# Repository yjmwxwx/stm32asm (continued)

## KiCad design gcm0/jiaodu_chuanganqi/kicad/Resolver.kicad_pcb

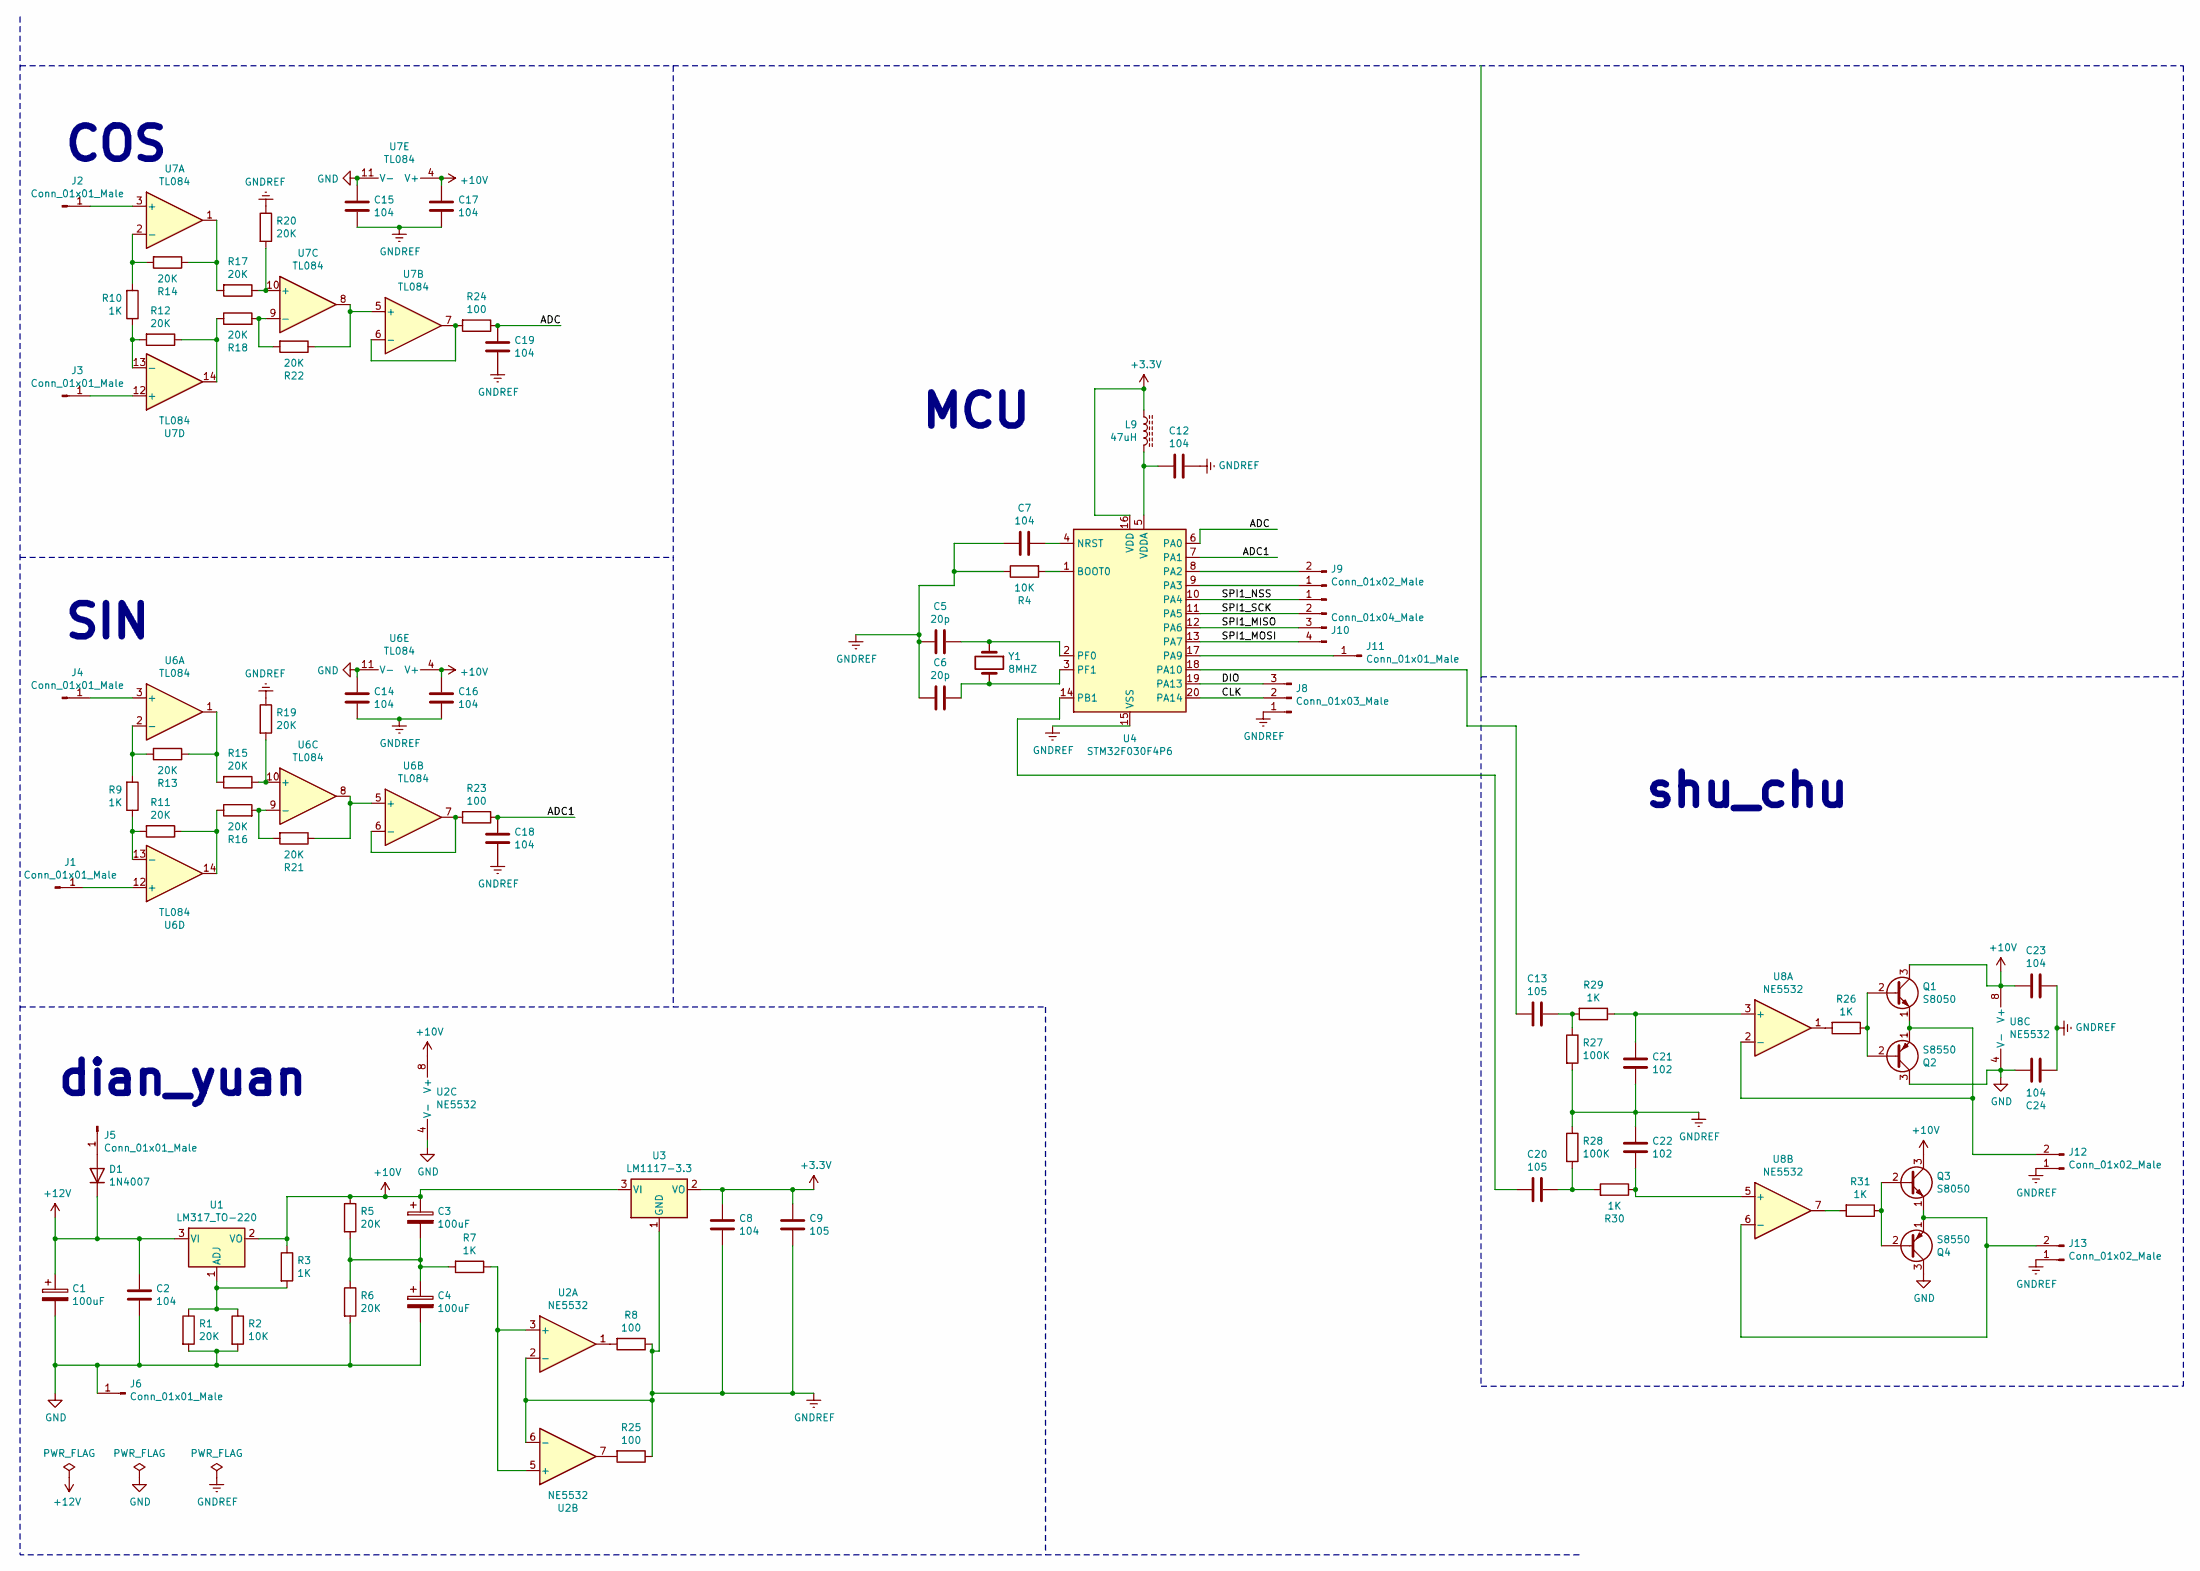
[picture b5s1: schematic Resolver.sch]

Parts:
C1, C3, C4: 100uF; CP_Radial_D5.0mm_P2.00mm
C2, C7, C8, C12, C14, C15, C16, C17, C18, C19, C23, C24: 104; C_Disc_D4.7mm_W2.5mm_P5.00mm
C5, C6: 20p; C_0805_2012Metric_Pad1.18x1.45mm_HandSolder
C9, C13, C20: 105; C_0805_2012Metric_Pad1.18x1.45mm_HandSolder
C21, C22: 102; C_Disc_D7.5mm_W5.0mm_P10.00mm
D1: 1N4007; D_DO-41_SOD81_P10.16mm_Horizontal
J1, J2, J3, J4, J5, J6, J11: Conn_01x01_Male; PinHeader_1x01_P2.54mm_Vertical
J8: Conn_01x03_Male; PinHeader_1x03_P2.54mm_Vertical
J9, J12, J13: Conn_01x02_Male; PinHeader_1x02_P2.54mm_Vertical
J10: Conn_01x04_Male; PinHeader_1x04_P2.54mm_Vertical
L9: 47uH; L_Taiyo-Yuden_MD-5050
Q1, Q3: S8050; TO-92_Inline
Q2, Q4: S8550; TO-92_Inline
R1, R5, R6, R11, R12, R13, R14, R15, R16, R17, R18, R19, R20, R21, R22: 20K; R_Axial_DIN0207_L6.3mm_D2.5mm_P10.16mm_Horizontal
R2, R4: 10K; R_Axial_DIN0207_L6.3mm_D2.5mm_P10.16mm_Horizontal
R3, R7, R9, R10, R26, R29, R30, R31: 1K; R_Axial_DIN0207_L6.3mm_D2.5mm_P10.16mm_Horizontal
R8, R23, R24, R25: 100; R_Axial_DIN0207_L6.3mm_D2.5mm_P10.16mm_Horizontal
R27, R28: 100K; R_Axial_DIN0207_L6.3mm_D2.5mm_P10.16mm_Horizontal
U1: LM317_TO-220; TO-220-3_Vertical
U2, U8: NE5532; DIP-8_W7.62mm
U3: LM1117-3.3; SOT-223-3_TabPin2
U4: STM32F030F4P6; TSSOP-20_4.4x6.5mm_P0.65mm
U6, U7: TL084; DIP-14_W7.62mm
Y1: 8MHZ; Crystal_HC49-4H_Vertical

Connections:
+3V3: C8.1, C9.1, L9.2, U3.2 (VO), U4.16 (VDD)
+10V: C3.1, C16.1, C17.1, C23.2, Q1.3 (C), Q3.3 (C), R3.1, R5.1, U1.2 (VO), U2.8 (V+), U3.3 (VI), U6.4 (V+), U7.4 (V+), U8.8 (V+)
+12V: C1.1, C2.1, D1.1 (K), U1.3 (VI)
/ADC: C19.1, R24.1, U4.6 (PA0)
/ADC1: C18.1, R23.1, U4.7 (PA1)
/CLK: J8.2, U4.20 (PA14)
/DIO: J8.3, U4.19 (PA13)
/SPI1_MISO: J10.3, U4.12 (PA6)
/SPI1_MOSI: J10.4, U4.13 (PA7)
/SPI1_NSS: J10.1, U4.10 (PA4)
/SPI1_SCK: J10.2, U4.11 (PA5)
GND: C1.2, C2.2, C4.2, C14.1, C15.1, C24.2, J6.1, Q2.3 (C), Q4.3 (C), R1.2, R2.2, R6.2, U2.4 (V-), U6.11 (V-), U7.11 (V-), U8.4 (V-)
GNDREF: C5.2, C6.2, C7.2, C8.2, C9.2, C12.1, C14.2, C15.2, C16.2, C17.2, C18.2, C19.2, C21.1, C22.1, C23.1, C24.1, J8.1, J12.1, J13.1, R4.1, R8.1, R19.1, R20.1, R25.1, R27.2, R28.1, U2.2 (-), U2.6 (-), U3.1 (GND), U4.15 (VSS)
unnamed: C3.2, C4.1, R5.2, R6.1, R7.2
unnamed: C5.1, U4.2 (PF0), Y1.1
unnamed: C6.1, U4.3 (PF1), Y1.2
unnamed: C7.1, U4.4 (NRST)
unnamed: C12.2, L9.1, U4.5 (VDDA)
unnamed: C13.1, R27.1, R29.2
unnamed: C13.2, U4.18 (PA10)
unnamed: C20.1, R28.2, R30.2
unnamed: C20.2, U4.14 (PB1)
unnamed: C21.2, R29.1, U8.3 (+)
unnamed: C22.2, R30.1, U8.5 (+)
unnamed: D1.2 (A), J5.1
unnamed: J1.1, U6.12 (+)
unnamed: J2.1, U7.3 (+)
unnamed: J3.1, U7.12 (+)
unnamed: J4.1, U6.3 (+)
unnamed: J9.1, U4.9 (PA3)
unnamed: J9.2, U4.8 (PA2)
unnamed: J11.1, U4.17 (PA9)
unnamed: J12.2, Q1.1 (E), Q2.1 (E), U8.2 (-)
unnamed: J13.2, Q3.1 (E), Q4.1 (E), U8.6 (-)
unnamed: Q1.2 (B), Q2.2 (B), R26.1
unnamed: Q3.2 (B), Q4.2 (B), R31.1
unnamed: R1.1, R2.1, R3.2, U1.1 (ADJ)
unnamed: R4.2, U4.1 (BOOT0)
unnamed: R7.1, U2.3 (+), U2.5 (+)
unnamed: R8.2, U2.1
unnamed: R10.1, R12.2, U7.13 (-)
unnamed: R10.2, R14.2, U7.2 (-)
unnamed: R11.1, R16.1, U6.14
unnamed: R9.1, R11.2, U6.13 (-)
unnamed: R12.1, R18.1, U7.14
unnamed: R13.1, R15.2, U6.1
unnamed: R9.2, R13.2, U6.2 (-)
unnamed: R14.1, R17.2, U7.1
unnamed: R15.1, R19.2, U6.10 (+)
unnamed: R16.2, R21.2, U6.9 (-)
unnamed: R17.1, R20.2, U7.10 (+)
unnamed: R18.2, R22.2, U7.9 (-)
unnamed: R21.1, U6.5 (+), U6.8
unnamed: R22.1, U7.5 (+), U7.8
unnamed: R23.2, U6.6 (-), U6.7
unnamed: R24.2, U7.6 (-), U7.7
unnamed: R25.2, U2.7
unnamed: R26.2, U8.1
unnamed: R31.2, U8.7

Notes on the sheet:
COS
SIN
shu_chu
MCU
dian_yuan

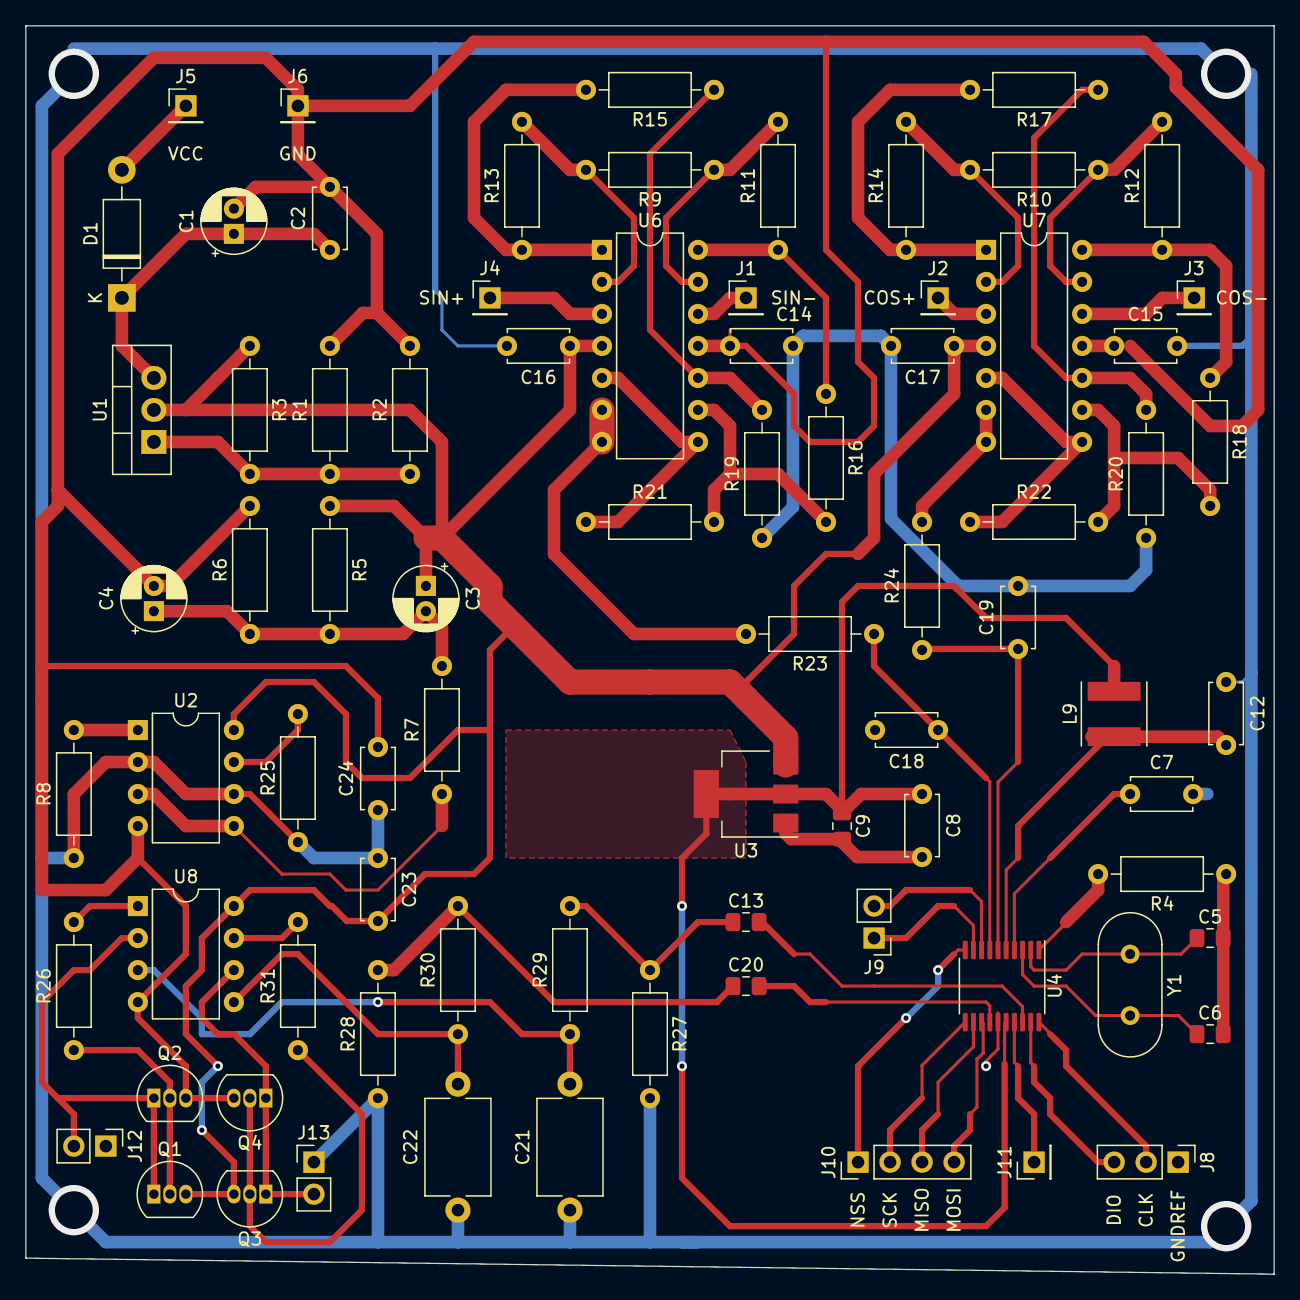
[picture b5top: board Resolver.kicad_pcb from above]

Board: 2 copper layers, 99.1 x 99.1 mm, 79 parts (0 on the bottom side), 59 nets.

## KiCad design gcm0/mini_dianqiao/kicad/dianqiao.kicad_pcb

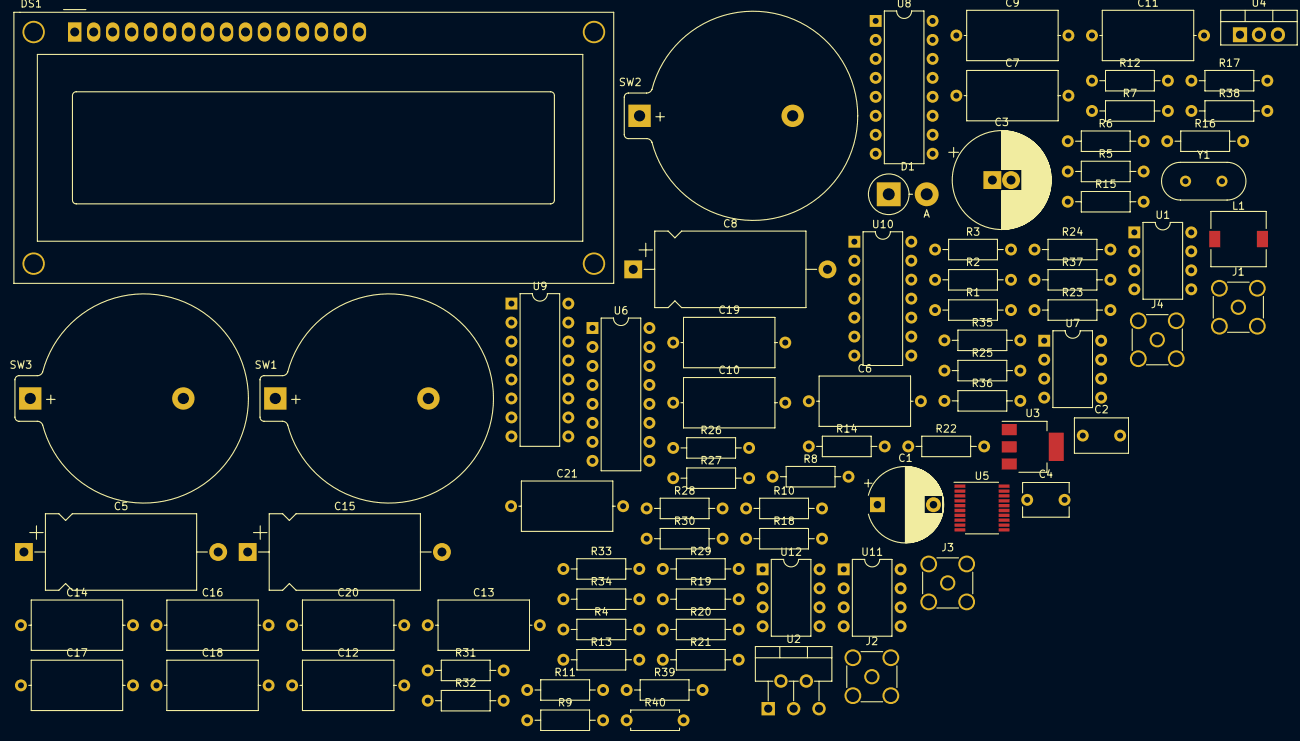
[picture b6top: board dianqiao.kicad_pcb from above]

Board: 2 copper layers, 84 parts (0 on the bottom side), 67 nets, no tracks yet.

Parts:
C1: 100uF; CP_Radial_D10.0mm_P7.50mm
C2: 104; C_Rect_L7.0mm_W4.5mm_P5.00mm
C3: 1000uF; CP_Radial_D13.0mm_P2.50mm
C4: 104; C_Disc_D6.0mm_W4.4mm_P5.00mm
C5, C8: 100uF; CP_Axial_L20.0mm_D10.0mm_P26.00mm_Horizontal
C6, C7, C9, C17: 104; C_Axial_L12.0mm_D6.5mm_P15.00mm_Horizontal
C10: 106; C_Axial_L12.0mm_D6.5mm_P15.00mm_Horizontal
C11, C12, C21: 101; C_Axial_L12.0mm_D6.5mm_P15.00mm_Horizontal
C13: 22P; C_Axial_L12.0mm_D6.5mm_P15.00mm_Horizontal
C14: 22p; C_Axial_L12.0mm_D6.5mm_P15.00mm_Horizontal
C15: 4.7uF; CP_Axial_L20.0mm_D10.0mm_P26.00mm_Horizontal
C16, C18: 103; C_Axial_L12.0mm_D6.5mm_P15.00mm_Horizontal
C19: 68; C_Axial_L12.0mm_D6.5mm_P15.00mm_Horizontal
C20: 331; C_Axial_L12.0mm_D6.5mm_P15.00mm_Horizontal
D1: 1N5822; D_DO-201AD_P5.08mm_Vertical_AnodeUp
DS1: WC1602A
J1, J2, J3, J4: Conn_Coaxial; SMA_Amphenol_901-144_Vertical
L1: 100uH; L_7.3x7.3_H3.5
R1, R7, R24, R25, R27, R29: 1K; R_Axial_DIN0207_L6.3mm_D2.5mm_P10.16mm_Horizontal
R2: 333; R_Axial_DIN0207_L6.3mm_D2.5mm_P10.16mm_Horizontal
R3: 200; R_Axial_DIN0207_L6.3mm_D2.5mm_P10.16mm_Horizontal
R4, R5, R6, R28, R36, R37: 100; R_Axial_DIN0207_L6.3mm_D2.5mm_P10.16mm_Horizontal
R8, R10, R11, R12, R13, R14, R15, R17, R18, R34, R35: 10K; R_Axial_DIN0207_L6.3mm_D2.5mm_P10.16mm_Horizontal
R9, R16: 100K; R_Axial_DIN0207_L6.3mm_D2.5mm_P10.16mm_Horizontal
R19, R20, R22, R23, R32, R33: 20K; R_Axial_DIN0207_L6.3mm_D2.5mm_P10.16mm_Horizontal
R21, R26: 9K; R_Axial_DIN0207_L6.3mm_D2.5mm_P10.16mm_Horizontal
R30, R38: 20k; R_Axial_DIN0207_L6.3mm_D2.5mm_P10.16mm_Horizontal
R31: 100k; R_Axial_DIN0207_L6.3mm_D2.5mm_P10.16mm_Horizontal
R39: 10k; R_Axial_DIN0207_L6.3mm_D2.5mm_P10.16mm_Horizontal
R40: 10K; R_Axial_DIN0207_L6.3mm_D2.5mm_P7.62mm_Horizontal
SW1: 2; BatteryHolder_Keystone_107_1x23mm
SW2: 0; BatteryHolder_Keystone_107_1x23mm
SW3: 1; BatteryHolder_Keystone_107_1x23mm
U1, U7, U11, U12: NE5532; DIP-8_W7.62mm
U2: LM2596T-ADJ; TO-220-5_P3.4x3.7mm_StaggerOdd_Lead3.8mm_Vertical
U3: LM1117-3.3; SOT-223-3_TabPin2
U4: LM7805_TO220; TO-220-3_Vertical
U5: STM32F030F4P6; TSSOP-20_4.4x6.5mm_P0.65mm
U6: CD4052B; DIP-16_W7.62mm
U8: CD4053B; DIP-16_W7.62mm
U9: 74HC595; DIP-16_W7.62mm
U10: TL084; DIP-14_W7.62mm
Y1: 8M; Crystal_HC49-U_Vertical

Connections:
+3.3: U5.5, U5.16
+3V3: C9.1, C10.1, U3.2
+5V: C7.1, C8.1, DS1.2, DS1.15, R10.2, R12.1, R15.1, R17.1, R18.2, U3.3, U4.3, U6.16, U7.8, U8.16, U9.10, U9.16, U10.4, U11.8, U12.8
+9V: C1.1, C2.1, C5.1, C6.2, U2.1, U4.1
-5V: C3.2, C4.2, D1.2, R2.2, U2.3, U2.5, U6.7, U7.4, U8.7, U10.11, U11.4, U12.4
ADC1: C18.1, R36.1, U5.6
ADC2: C16.1, R37.1, U5.7
GND: C1.2, C2.2, C3.1, C4.1, C5.2, C6.1, C7.2, C8.2, C9.2, C10.2, C11.2, C12.2, C13.2, C14.2, C16.2, C17.2, C18.2, C19.2, C21.2, DS1.1, DS1.5, J1.1, J2.1, J3.1, J4.1, L1.1, R1.1, R14.2, R16.2, R22.1, R24.2, R25.2, R27.2, R29.2, R35.2, SW1.1, SW2.2, SW3.2, U3.1, U4.2, U5.15, U6.6, U6.8, U8.6, U8.8, U9.8, U9.13, U11.3, U12.5
unnamed: C11.1, R11.2, U1.5
unnamed: C12.1, R11.1, R13.2
unnamed: C13.1, U5.2, Y1.2
unnamed: C14.1, U5.3, Y1.1
unnamed: C15.2, R16.1, R40.1
unnamed: C17.1, U5.4
unnamed: C19.1, R30.2, R31.2, U1.3
unnamed: C20.1, R3.1, U1.1, U1.2
unnamed: C20.2, R30.1, R31.1, R38.2, R39.2
unnamed: C21.1, R13.1, R40.2
unnamed: D1.1, L1.2, U2.2
unnamed: DS1.3, R29.1
unnamed: DS1.4, U9.15
unnamed: DS1.6, U9.1
unnamed: DS1.11, U9.2
unnamed: DS1.12, U9.3
unnamed: DS1.13, U9.4
unnamed: DS1.14, U9.5
unnamed: DS1.16, R27.1
unnamed: J1.2, R3.2, R4.1
unnamed: J2.2, R4.2, U8.2
unnamed: J3.2, R5.1, U8.5
unnamed: J4.2, R5.2, R6.2, R7.2, R8.2, R9.2, R28.1, U8.3
unnamed: R1.2, R2.1, U2.4
unnamed: R6.1, U6.1, U6.12
unnamed: R7.1, U6.5, U6.14
unnamed: R8.1, U6.2, U6.15
unnamed: R9.1, U6.4, U6.11
unnamed: R14.1, U5.1
unnamed: R19.1, R22.2, U10.10
unnamed: R19.2, U10.13, U10.14
unnamed: R20.1, R23.2, U10.9
unnamed: R20.2, U10.1, U10.2
unnamed: R21.1, R23.1, U8.13, U10.8
unnamed: R21.2, R24.1, U8.12
unnamed: R25.1, R26.2, U10.6
unnamed: R26.1, U10.7, U12.3
unnamed: R28.2, U11.2
unnamed: R32.1, R33.2, U12.6
unnamed: R32.2, R37.2, U12.1, U12.2
unnamed: R33.1, R36.2, U12.7
unnamed: R34.1, R38.1, R39.1, U1.7
unnamed: R34.2, R35.1, U1.6
unnamed: SW1.2, U5.14
unnamed: SW2.1, U5.8
unnamed: SW3.1, U5.10
unnamed: U6.13, U8.1
unnamed: U8.4, U10.3
unnamed: U8.14, U10.5
unnamed: U8.15, U10.12
unnamed: U6.3, U11.1
PA3: R18.1, U5.9, U8.11
PA5: R15.2, U5.11, U9.11
PA6: R12.2, U5.12, U9.12
PA7: R17.2, U5.13, U9.14
PA9: R10.1, U5.17, U8.9, U8.10
SPWM: C15.1, U5.18
liang_cheng: U6.9, U9.6
liang_cheng1: U6.10, U9.7

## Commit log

2018-07-14 Create OSshiyan
2019-04-17 分立元件
2019-05-23 liangshi
2019-05-26 liangshi1
2019-05-27 liangshi2
2019-05-28 liangshi3
2019-06-03 liangshishumaguan
2019-06-04 liangshishumaguan_lvboqi_16
2019-06-04 liangshishumaguan_jianbo
2019-06-04 liangshishumaguan_shan_chu_1111.s
2019-06-05 liangshishumaguan_tupian
2019-06-06 liangshiwendubuchang
2019-06-09 liangshi-lcd
2019-06-17 ioshuchuspwm
2019-06-18 dingshiqispwm
2019-06-20 dingshiqispwm1
2019-06-22 重写计算幅度函数
2019-06-22 重写检波和计算幅度函数
2019-06-22 修改传感器函数
2019-06-22 adc256点采样
2019-06-23 adc256点FFT
2019-06-23 adc256点FFT成功！
2019-06-24 adc256点FFT电路图
2019-06-24 adc256点FFT实物图
2019-06-24 adc256点FFT改错误
2019-07-03 sa602测试
2019-07-10 NE602测试2
2019-07-13 NE602测试听到音频
2019-07-20 Cjy_JDxy电阻桥
2019-07-20 Cjy_JDxy电阻桥1
2019-07-20 Cjy_JDxy电阻桥电路图
2019-07-20 Cjy_JDxy电阻桥视频
2019-07-20 Cjy_JDxy电阻桥电路改错
2019-07-22 电路改错1
2019-07-26 接上称重传感器
2019-07-28 称重传感器
2019-07-28 称重传感器放大器温度补偿
2019-07-31 称重传感器放大器温度补偿1
2019-08-12 74hc595驱动1602
2019-08-15 加入相敏开关
2019-08-16 显示实部虚部
2019-08-17 显示实部虚部1
2019-08-22 显示实部虚部2
2019-08-22 显示实部虚部4
2019-08-22 显示实部虚部6
2019-08-23 显示上臂下臂实部虚部
2019-08-24 显示上臂下臂实部虚部1
2019-08-26 修改检波
2019-08-28 加入量程切换
2019-08-30 显示电阻值
2019-08-31 显示电阻成功
2019-09-01 阻抗计算
2019-09-02 修改自动量程
2019-09-05 检波改成DFT计算
2019-09-06 修改DFT函数
2019-09-06 修改DFT函数2
2019-09-06 修改正反相
2019-09-06 加入滤波器
2019-09-07 加入滤波器1
2019-09-08 加入放大电路
2019-09-11 修改放大电路
2019-09-16 修改除法
2019-09-17 64位除法
2019-09-25 修改阻抗计算函数
2019-09-25 手动量程
2019-10-19 试验设置几个量程
2019-10-22 成功测量几个量程的电容
2019-10-25 加入电感计算
2019-10-25 修改电容电感计算错误
2019-11-07 数码管LVDT
2019-11-08 显示位置成功
2019-11-09 修改原理图
2019-11-25 添加广告
2019-11-30 tingping
2019-12-09 平衡失败
2019-12-14 简单PID成功
2019-12-15 电子天平
2019-12-16 电子天平图片
2019-12-18 净水器冲洗定时器
2020-01-18 ne602差频
2020-01-20 阻抗分析仪
2020-01-24 定时器触发ADC
2020-02-04 菜集128点
2020-02-06 DMA成功
2020-02-08 dft函数改错
2020-02-09 阻抗表结果差不多
2020-02-09 实物图片
2020-02-10 电路改错
2020-02-13 ADC初始化改错
2020-02-15 加入透射
2020-07-10 金属探测器
2020-07-11 149MHZ测量阻抗
2020-07-21 探测金属管道缝隙成功
2020-07-24 按键校0
2020-07-24 按键校0改错
2020-08-01 阻抗数码管
2020-08-11 adc采样和DFT
2020-08-12 改电路改方案
2020-08-16 自动平衡桥方案失败
2020-08-17 实验RF-IV方案
2020-08-17 编写按键和菜单
2020-08-18 显示阻抗
2020-08-21 频率切换
2020-08-22 频率切换成功
2020-08-23 自动量程成功
2020-08-28 显示上下臂
2020-08-29 cordic_cos_sin
2020-08-31 相位和幅度矫正
2020-09-13 相位和幅度矫正成功
2020-09-16 电容显示
2020-10-16 相位旋转函数反转支持
2020-10-17 电感显示
2020-10-18 加自动换档延时
2021-01-02 添加lcd显示
2021-01-03 加入si5351驱动
2021-01-24 显示PLL
2021-01-24 乘法函数改错
2021-02-02 开始设计一个旋转变压器控制SI5351的信号发生器
2021-02-05 旋转变压器成功
2021-02-05 电路图改错
2021-02-06 添加实物图片
2021-02-07 相位补偿
2021-02-09 显示转速
2021-02-09 显示转速成功
2021-02-10 相位补偿成功
2021-02-23 旋转变压器解码
2021-02-27 画了PCB
2021-02-28 滤波器效率优化
2021-03-02 编写fir滤波器程序
2021-03-04 比例矫正
2021-03-05 角度差和P
2021-03-06 pi控制
2021-04-09 修补滤波器BUG
2021-04-22 pmsm电机
2021-04-26 加入旋转变压器
2021-04-27 让电机转
2021-04-28 svpwm
2021-04-29 svpwm1
2021-04-30 电机转了
2021-04-30 svpwm两个电压参与计算
2021-07-07 磁通门ADC采样
2021-07-17 删掉无用文件
2021-07-17 删掉无用文件1
2021-08-04 PCB1
2021-08-08 SPI_74HC595
2021-08-13 量程改错
2021-08-14 100KHZ自动量程
2021-08-18 增加多个频率
2021-08-18 频率切换改错
2021-08-19 频率切换改错1
2021-08-20 1KHZ正弦表修改
2021-08-23 +-5V版电路图
2021-08-23 电路少画一个电阻
2021-08-23 电路偏置改错
2021-08-23 修改小数点位置
2021-09-01 LM2596延迟电路
2021-09-04 调整档位
2021-12-08 修改频率切换程序
2022-01-02 运放4580版LCR
2022-01-04 相位幅度矫正框架
2022-01-06 相位幅度校准程序成功
2022-01-08 修改100KHZ的ADC触发方式
2022-01-10 档位设置
2022-01-13 修改上下臂切换程序
2022-01-14 电路有问题
2022-01-14 dft改错
2022-01-16 修改采样率
2022-01-18 校准程序框架
2022-01-19 校准程序编写完成
2022-01-19 电容显示框架
2022-01-20 电容显示写完
2022-01-21 读校准表
2022-01-23 校准实验
2022-01-23 自动档位改错
2022-01-31 osm校准
2022-02-03 编写OSM校准程序
2022-02-03 OSM校准程序写完
2022-02-04 校准显示改错
2022-02-06 OSM程序改错
2022-02-08 ESR表
2022-02-12 电感小数点改错
2022-02-16 esr电路改错
2022-02-16 lcr_5
2022-02-20 修改电路
2022-02-23 修改滤波电路
2022-03-06 修改模拟电路
2022-04-08 修改三倍衰减电阻
2022-04-12 单锂电池版
2023-03-05 电池内阻仪
2023-03-23 画了PCB写了校准程序
2023-03-25 画了个KICAD原理图
2023-03-26 降低刷新速度到3.9秒一次
2023-03-26 采样率改成100KHZ
2023-04-04 电池供电版
2023-04-11 降低功耗版
2023-04-13 修改KICAD原理图标注错误
2023-04-17 PCB改错
2023-04-17 PCB改错1
2023-05-04 1万字COG12864显示
2023-05-04 DFT堆栈错误修改
2023-08-01 实部和虚部分离显示30000字版本
